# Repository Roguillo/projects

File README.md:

For personal and academic projects

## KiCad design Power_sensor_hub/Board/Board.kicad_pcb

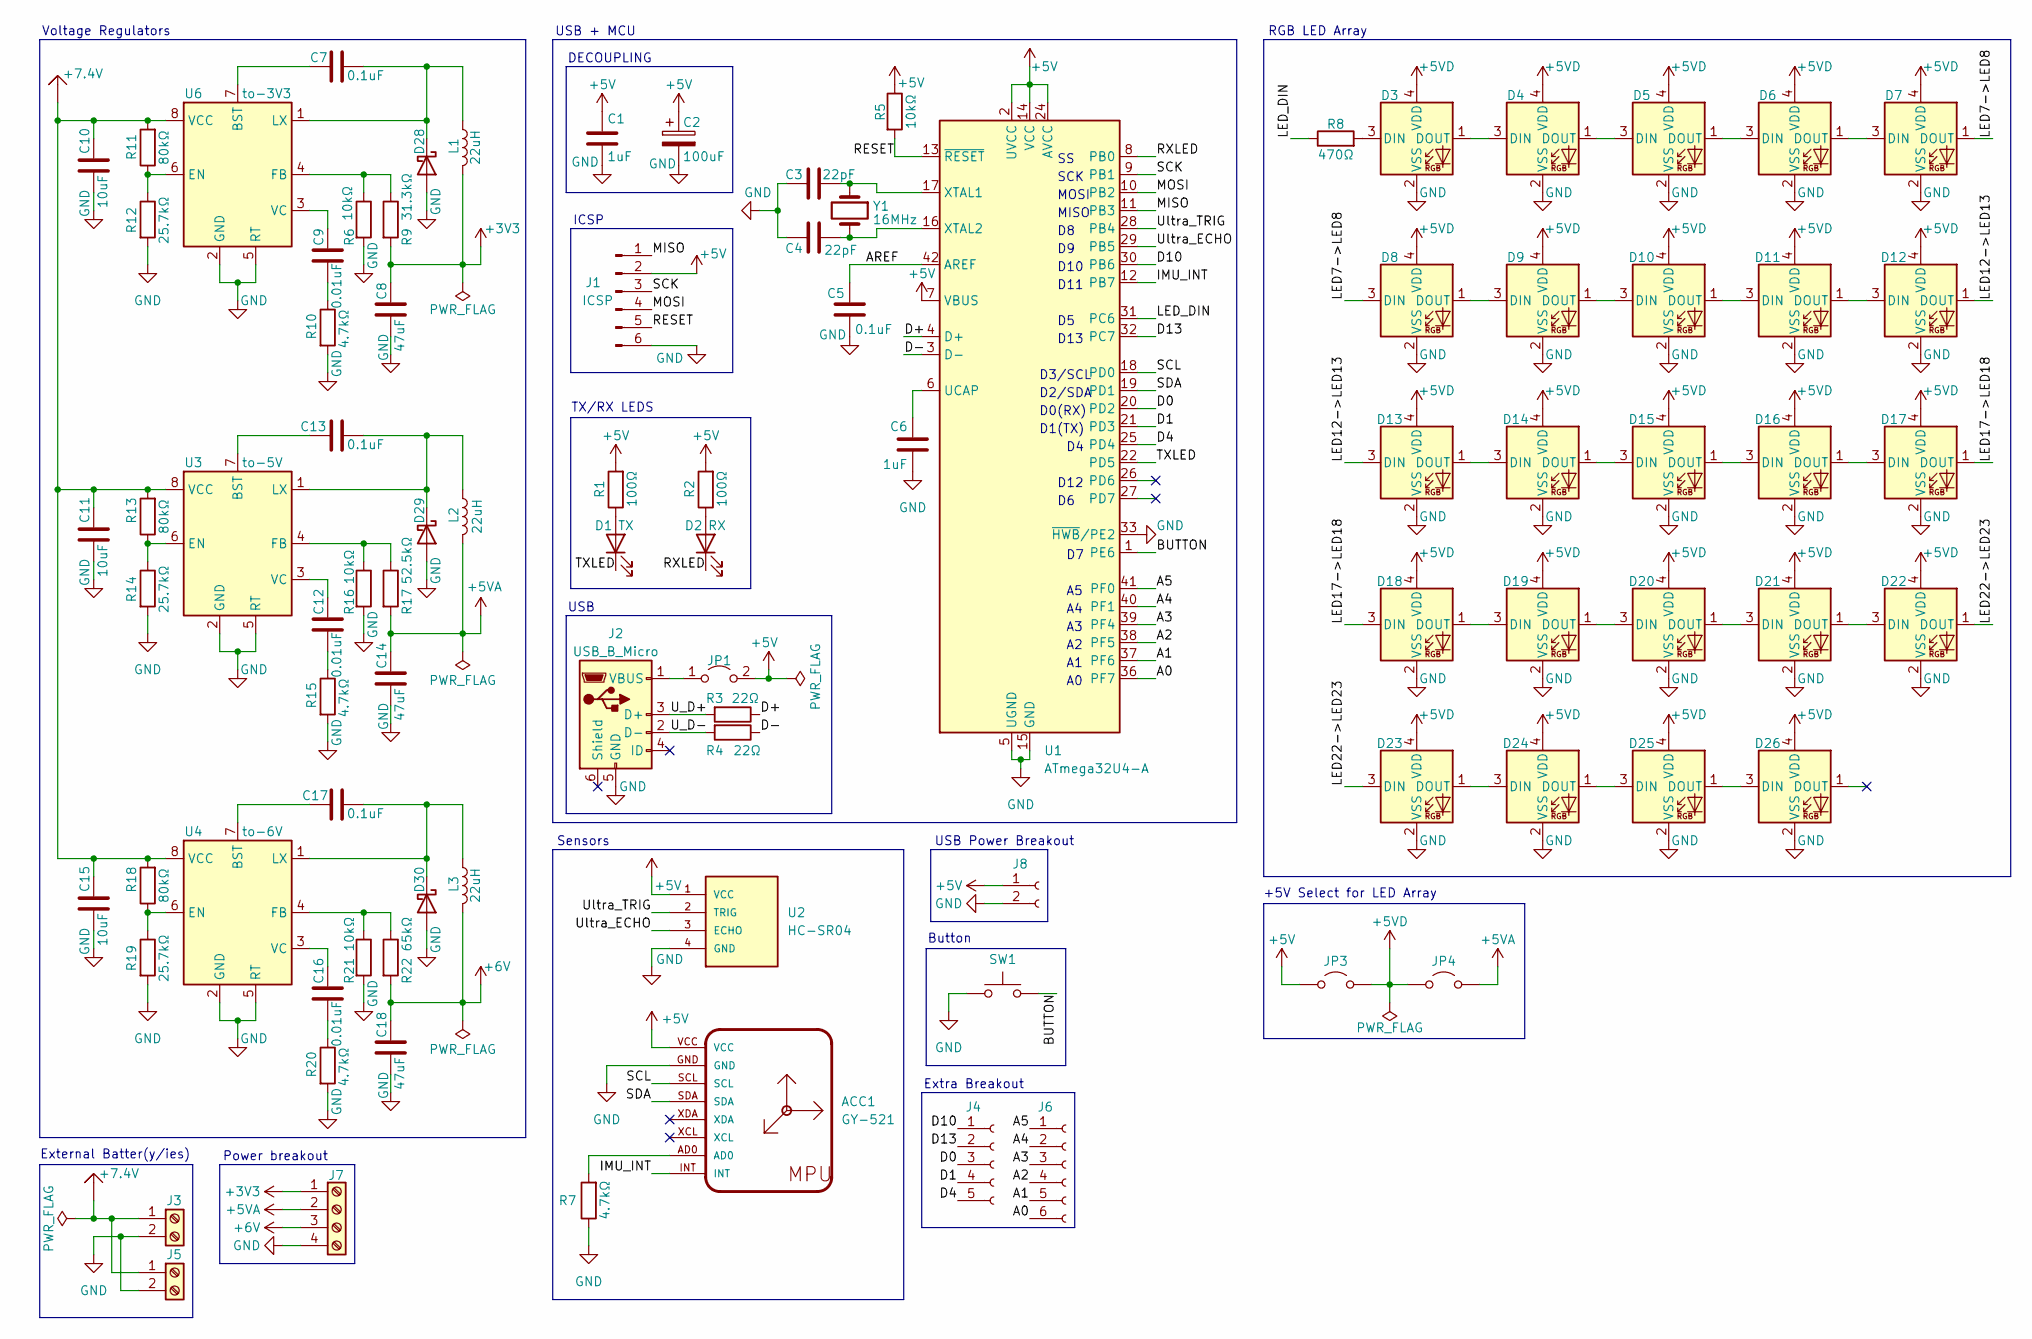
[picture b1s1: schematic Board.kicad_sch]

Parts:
ACC1: GY-521
C1, C6: 1uF; C_0805_2012Metric_Pad1.18x1.45mm_HandSolder
C2: 100uF; CP_Elec_5x5.3
C3, C4: 22pF; C_0805_2012Metric_Pad1.18x1.45mm_HandSolder
C5: 0.1uF; C_0805_2012Metric_Pad1.18x1.45mm_HandSolder
C7, C13, C17: 0.1uF; C_0603_1608Metric_Pad1.08x0.95mm_HandSolder
C8, C14, C18: 47uF; C_1206_3216Metric_Pad1.33x1.80mm_HandSolder
C9, C12, C16: 0.01uF; C_0603_1608Metric_Pad1.08x0.95mm_HandSolder
C10, C11, C15: 10uF; C_1206_3216Metric_Pad1.33x1.80mm_HandSolder
D1: TX; LED_0805_2012Metric_Pad1.15x1.40mm_HandSolder
D2: RX; LED_0805_2012Metric_Pad1.15x1.40mm_HandSolder
D3, D4, D5, D6, D7, D8, D9, D10, D11, D12, D13, D14, D15, D16, D17, D18, D19, D20, D21, D22, D23, D24, D25, D26: SK6812MINI; LED_SK6812MINI_PLCC4_3.5x3.5mm_P1.75mm
D28, D29, D30: D_2114_3652Metric_Pad1.85x3.75mm_HandSolder
J1: ICSP; PinHeader_2x03_P2.54mm_Vertical
J2: USB_B_Micro; USB_Micro-B_GCT_USB3076-30-A
J3, J5: TerminalBlock_Altech_AK300-2_P5.00mm
J4: PinHeader_1x05_P2.54mm_Vertical
J6: PinHeader_1x06_P2.54mm_Vertical
J7: TerminalBlock_Altech_AK300-4_P5.00mm
J8: PinHeader_1x02_P2.54mm_Vertical
JP1: Jumper_2_Open; SolderJumper-2_P1.3mm_Open_TrianglePad1.0x1.5mm
JP3, JP4: SolderJumper-2_P1.3mm_Open_TrianglePad1.0x1.5mm
L1, L2, L3: 22uH; IND_CLF12577NIT_12P8X12P5_TDK-M
R1, R2: 100Ω; R_0805_2012Metric_Pad1.20x1.40mm_HandSolder
R3, R4: 22Ω; R_0805_2012Metric_Pad1.20x1.40mm_HandSolder
R5: 10kΩ; R_0805_2012Metric_Pad1.20x1.40mm_HandSolder
R6, R16, R21: 10kΩ; R_0603_1608Metric_Pad0.98x0.95mm_HandSolder
R7, R10, R15, R20: 4.7kΩ; R_0603_1608Metric_Pad0.98x0.95mm_HandSolder
R8: 470Ω; R_0805_2012Metric_Pad1.20x1.40mm_HandSolder
R9: 31.3kΩ; R_0603_1608Metric_Pad0.98x0.95mm_HandSolder
R11, R13, R18: 80kΩ; R_0402_1005Metric_Pad0.72x0.64mm_HandSolder
R12, R14, R19: 25.7kΩ; R_0603_1608Metric_Pad0.98x0.95mm_HandSolder
R17: 52.5kΩ; R_0603_1608Metric_Pad0.98x0.95mm_HandSolder
R22: 65kΩ; R_0603_1608Metric_Pad0.98x0.95mm_HandSolder
SW1: SW_SPST_PTS647_Sx38
U1: ATmega32U4-A; TQFP-44_10x10mm_P0.8mm
U2: HC-SR04; PinHeader_1x04_P2.54mm_Vertical
U3: to-5V; HTSOP-8-1EP_3.9x4.9mm_P1.27mm_EP2.4x3.2mm_ThermalVias
U4: to-6V; HTSOP-8-1EP_3.9x4.9mm_P1.27mm_EP2.4x3.2mm_ThermalVias
U6: to-3V3; HTSOP-8-1EP_3.9x4.9mm_P1.27mm_EP2.4x3.2mm_ThermalVias
Y1: 16MHz; Crystal_SMD_5032-2Pin_5.0x3.2mm

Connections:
+3V3: C8.1, J7.1, L1.2, R9.2
+5V: ACC1.VCC, C1.1, C2.1, J1.2, J8.1, JP1.2 (B), JP3.1 (A), R1.2, R2.2, R5.1, U1.2 (UVCC), U1.7 (VBUS), U1.14 (VCC), U1.24 (AVCC), U1.34 (VCC), U1.44 (AVCC), U2.1 (VCC)
+5VA: C14.1, J7.2, JP4.2 (B), L2.2, R17.2
+5VD: D3.4 (VDD), D4.4 (VDD), D5.4 (VDD), D6.4 (VDD), D7.4 (VDD), D8.4 (VDD), D9.4 (VDD), D10.4 (VDD), D11.4 (VDD), D12.4 (VDD), D13.4 (VDD), D14.4 (VDD), D15.4 (VDD), D16.4 (VDD), D17.4 (VDD), D18.4 (VDD), D19.4 (VDD), D20.4 (VDD), D21.4 (VDD), D22.4 (VDD), D23.4 (VDD), D24.4 (VDD), D25.4 (VDD), D26.4 (VDD), JP3.2 (B), JP4.1 (A)
+6V: C18.1, J7.3, L3.2, R22.2
+7.4V: C10.1, C11.1, C15.1, J3.1, J5.1, R11.2, R13.2, R18.2, U3.8 (VCC), U4.8 (VCC), U6.8 (VCC)
/A0: J6.6, U1.36 (PF7)
/A1: J6.5, U1.37 (PF6)
/A2: J6.4, U1.38 (PF5)
/A3: J6.3, U1.39 (PF4)
/A4: J6.2, U1.40 (PF1)
/A5: J6.1, U1.41 (PF0)
/AREF: C5.1, U1.42 (AREF)
/BUTTON: SW1.2, U1.1 (PE6)
/D0: J4.3, U1.20 (PD2)
/D1: J4.4, U1.21 (PD3)
/D4: J4.5, U1.25 (PD4)
/D10: J4.1, U1.30 (PB6)
/D13: J4.2, U1.32 (PC7)
/D+: R3.1, U1.4 (D+)
/D-: R4.1, U1.3 (D-)
/IMU_INT: ACC1.INT, U1.12 (PB7)
/LED7->LED8: D7.1 (DOUT), D8.3 (DIN)
/LED12->LED13: D12.1 (DOUT), D13.3 (DIN)
/LED17->LED18: D17.1 (DOUT), D18.3 (DIN)
/LED22->LED23: D22.1 (DOUT), D23.3 (DIN)
/LED_DIN: R8.1, U1.31 (PC6)
/MISO: J1.1, U1.11 (PB3)
/MOSI: J1.4, U1.10 (PB2)
/RESET: J1.5, R5.2, U1.13 (~RESET)
/RXLED: D2.1 (K), U1.8 (PB0)
/SCK: J1.3, U1.9 (PB1)
/SCL: ACC1.SCL, U1.18 (PD0)
/SDA: ACC1.SDA, U1.19 (PD1)
/TXLED: D1.1 (K), U1.22 (PD5)
/U_D+: J2.3 (D+), R3.2
/U_D-: J2.2 (D-), R4.2
/Ultra_ECHO: U1.29 (PB5), U2.3 (ECHO)
/Ultra_TRIG: U1.28 (PB4), U2.2 (TRIG)
BST_3V3: C7.1, U6.7 (BST)
BST_5V: C13.1, U3.7 (BST)
BST_6V: C17.1, U4.7 (BST)
GND: ACC1.GND, C1.2, C2.2, C3.2, C4.2, C5.2, C6.2, C8.2, C10.2, C11.2, C14.2, C15.2, C18.2, D3.2 (VSS), D4.2 (VSS), D5.2 (VSS), D6.2 (VSS), D7.2 (VSS), D8.2 (VSS), D9.2 (VSS), D10.2 (VSS), D11.2 (VSS), D12.2 (VSS), D13.2 (VSS), D14.2 (VSS), D15.2 (VSS), D16.2 (VSS), D17.2 (VSS), D18.2 (VSS), D19.2 (VSS), D20.2 (VSS), D21.2 (VSS), D22.2 (VSS), D23.2 (VSS), D24.2 (VSS), D25.2 (VSS), D26.2 (VSS), D28.2 (A), D29.2 (A), D30.2 (A), J1.6, J2.5 (GND), J3.2, J5.2, J7.4, J8.2, R6.2, R7.1, R10.2, R12.2, R14.2, R15.2, R16.2, R19.2, R20.2, R21.2, SW1.1, U1.5 (UGND), U1.15 (GND), U1.23 (GND), U1.33 (~HWB/PE2), U1.35 (GND), U1.43 (GND), U2.4 (GND), U3.2 (GND), U3.5 (RT), U3.9, U4.2 (GND), U4.5 (RT), U4.9, U6.2 (GND), U6.5 (RT), U6.9; also elsewhere on the board
unnamed: ACC1.AD0, R7.2
unnamed: C9.2, R10.1
unnamed: C12.2, R15.1
unnamed: C16.2, R20.1
unnamed: D1.2 (A), R1.1
unnamed: D2.2 (A), R2.1
unnamed: D3.3 (DIN), R8.2
unnamed: D3.1 (DOUT), D4.3 (DIN)
unnamed: D4.1 (DOUT), D5.3 (DIN)
unnamed: D5.1 (DOUT), D6.3 (DIN)
unnamed: D6.1 (DOUT), D7.3 (DIN)
unnamed: D8.1 (DOUT), D9.3 (DIN)
unnamed: D9.1 (DOUT), D10.3 (DIN)
unnamed: D10.1 (DOUT), D11.3 (DIN)
unnamed: D11.1 (DOUT), D12.3 (DIN)
unnamed: D13.1 (DOUT), D14.3 (DIN)
unnamed: D14.1 (DOUT), D15.3 (DIN)
unnamed: D15.1 (DOUT), D16.3 (DIN)
unnamed: D16.1 (DOUT), D17.3 (DIN)
unnamed: D18.1 (DOUT), D19.3 (DIN)
unnamed: D19.1 (DOUT), D20.3 (DIN)
unnamed: D20.1 (DOUT), D21.3 (DIN)
unnamed: D21.1 (DOUT), D22.3 (DIN)
unnamed: D23.1 (DOUT), D24.3 (DIN)
unnamed: D24.1 (DOUT), D25.3 (DIN)
unnamed: D25.1 (DOUT), D26.3 (DIN)
unnamed: C7.2, D28.1 (K), L1.1, U6.1 (LX)
unnamed: C13.2, D29.1 (K), L2.1, U3.1 (LX)
unnamed: C17.2, D30.1 (K), L3.1, U4.1 (LX)
unnamed: J2.1 (VBUS), JP1.1 (A)
unnamed: C6.1, U1.6 (UCAP)
unnamed: C3.1, U1.17 (XTAL1), Y1.1
unnamed: C4.1, U1.16 (XTAL2), Y1.2
unnamed: R13.1, R14.1, U3.6 (EN)
unnamed: R16.1, R17.1, U3.4 (FB)
unnamed: C12.1, U3.3 (VC)
unnamed: R18.1, R19.1, U4.6 (EN)
unnamed: R21.1, R22.1, U4.4 (FB)
unnamed: C16.1, U4.3 (VC)
unnamed: R11.1, R12.1, U6.6 (EN)
unnamed: R6.1, R9.1, U6.4 (FB)
unnamed: C9.1, U6.3 (VC)

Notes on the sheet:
D13
RGB LED Array
D11
USB
Voltage Regulators
D0(RX)
D2/SDA
External Batter(y/ies)
SCK
DECOUPLING
Power breakout
MOSI
USB + MCU
Extra Breakout
Button
USB Power Breakout
D3/SCL
Sensors
MISO
D10
TX/RX LEDS
ICSP
D12
D1(TX)
+5V Select for LED Array

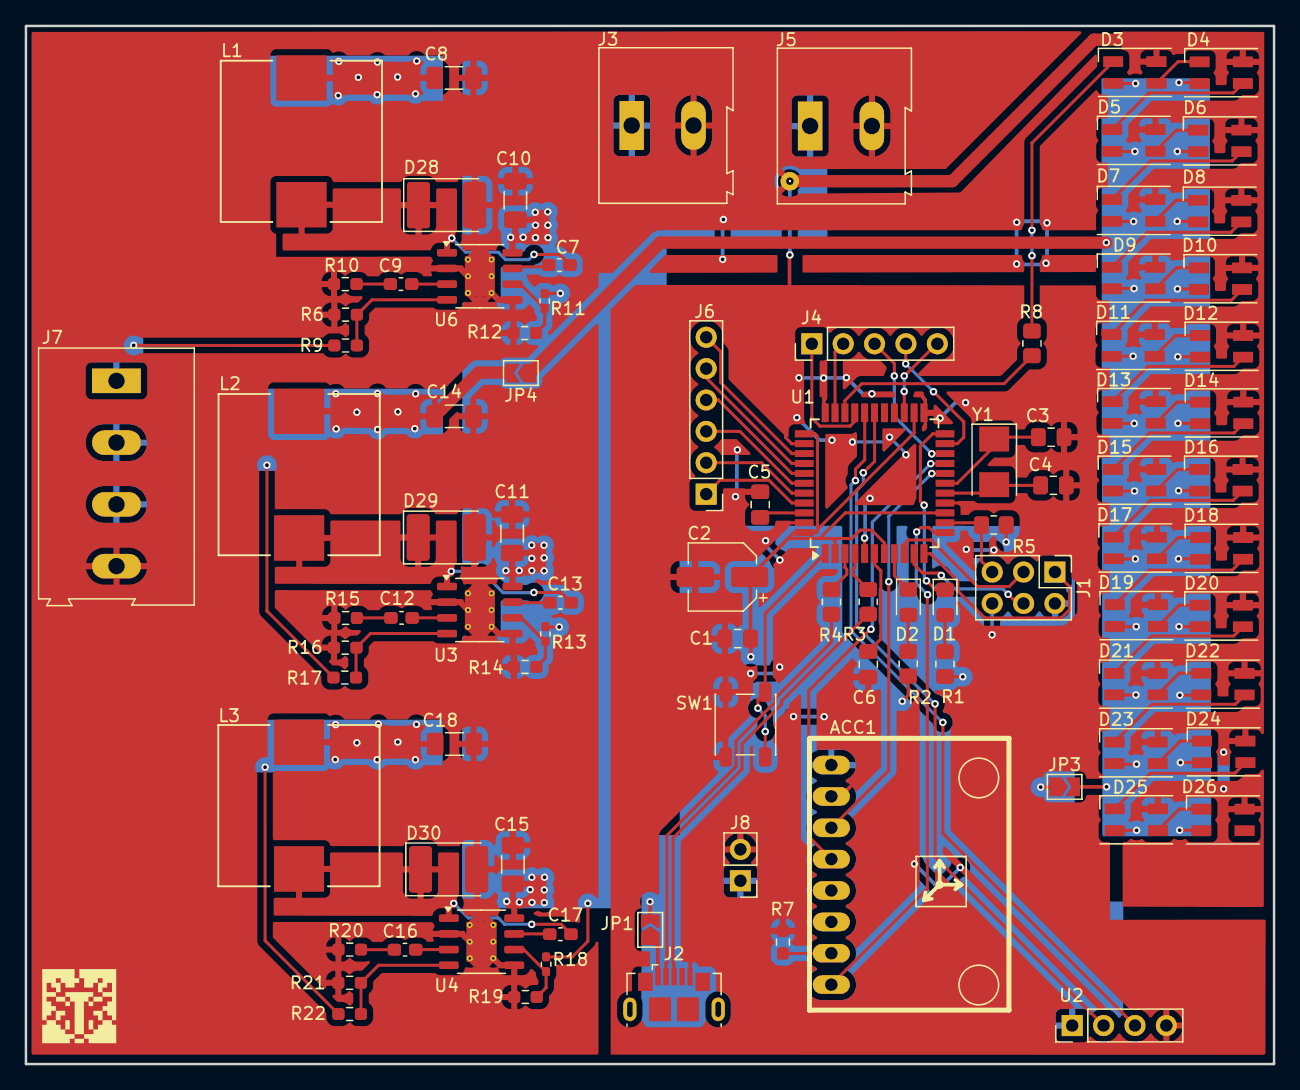
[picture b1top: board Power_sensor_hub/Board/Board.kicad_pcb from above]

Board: 2 copper layers, 101.0 x 84.0 mm, 92 parts (0 on the bottom side), 85 nets.

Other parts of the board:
.: STAR

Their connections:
GND: ..3; also elsewhere on the board

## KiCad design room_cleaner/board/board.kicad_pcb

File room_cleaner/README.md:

A general-purpose differential drive base robot. Planning on implementing CV and possibly an arm in the future.

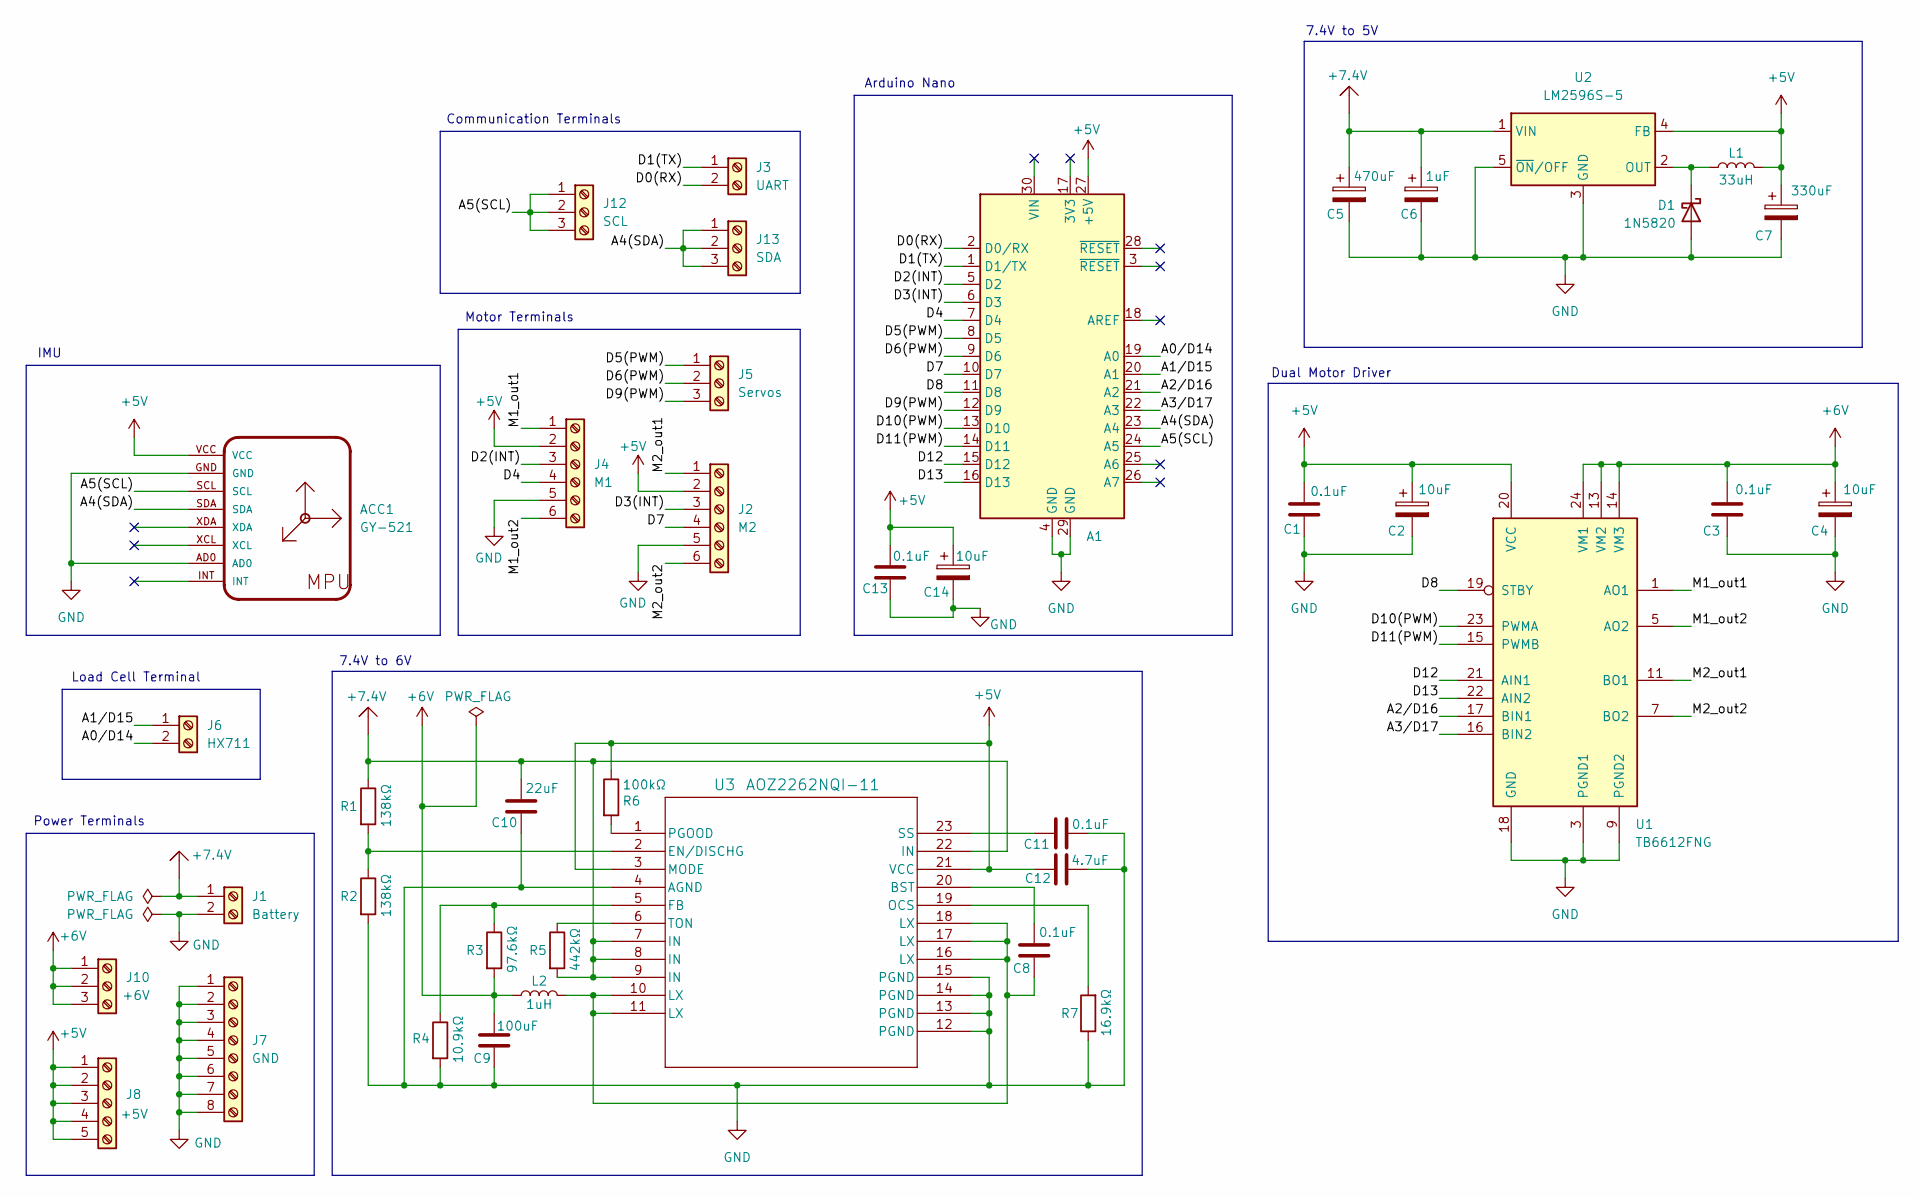
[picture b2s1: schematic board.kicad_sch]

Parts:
A1: Arduino_Nano
ACC1: GY-521
C1, C3, C8, C11, C13: 0.1uF; C_0402_1005Metric_Pad0.74x0.62mm_HandSolder
C2, C4, C14: 10uF; C_1206_3216Metric_Pad1.33x1.80mm_HandSolder
C5: 470uF; CP_Radial_D6.3mm_P2.50mm
C6: 1uF; C_0603_1608Metric_Pad1.08x0.95mm_HandSolder
C7: 330uF; CP_Radial_D6.3mm_P2.50mm
C9: 100uF; C_1206_3216Metric_Pad1.33x1.80mm_HandSolder
C10: 22uF; C_0603_1608Metric_Pad1.08x0.95mm_HandSolder
C12: 4.7uF; C_0603_1608Metric_Pad1.08x0.95mm_HandSolder
D1: 1N5820; D_DO-201AD_P15.24mm_Horizontal
J1: Battery; TerminalBlock_Altech_AK300-2_P5.00mm
J2: M2; TerminalBlock_bornier-6_P5.08mm
J3: UART; TerminalBlock_Altech_AK300-2_P5.00mm
J4: M1; TerminalBlock_bornier-6_P5.08mm
J5: Servos; TerminalBlock_Altech_AK300-3_P5.00mm
J6: HX711; TerminalBlock_Altech_AK300-2_P5.00mm
J7: GND; TerminalBlock_bornier-8_P5.08mm
J8: +5V; TerminalBlock_bornier-5_P5.08mm
J10: +6V; TerminalBlock_Altech_AK300-3_P5.00mm
J12: SCL; TerminalBlock_Altech_AK300-3_P5.00mm
J13: SDA; TerminalBlock_Altech_AK300-3_P5.00mm
L1: 33uH; L_6.3x6.3_H3
L2: 1uH; L_0805_2012Metric_Pad1.15x1.40mm_HandSolder
R1, R2: 138kΩ; R_0603_1608Metric_Pad0.98x0.95mm_HandSolder
R3: 97.6kΩ; R_0402_1005Metric_Pad0.72x0.64mm_HandSolder
R4: 10.9kΩ; R_0805_2012Metric_Pad1.20x1.40mm_HandSolder
R5: 442kΩ; R_0402_1005Metric_Pad0.72x0.64mm_HandSolder
R6: 100kΩ; R_0402_1005Metric_Pad0.72x0.64mm_HandSolder
R7: 16.9kΩ; R_0402_1005Metric_Pad0.72x0.64mm_HandSolder
U1: TB6612FNG; SSOP-24_5.3x8.2mm_P0.65mm
U2: LM2596S-5; TO-263-5_TabPin3
U3: AOZ2262NQI-11; AOZ226NQI-11

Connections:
+5V: A1.27 (+5V), ACC1.VCC, C1.1, C2.1, C7.1, C12.1, C13.1, C14.1, J2.2, J4.2, J8.1, J8.2, J8.3, J8.4, J8.5, L1.2, R6.1, U1.20 (VCC), U2.4 (FB), U3.3 (MODE), U3.21 (VCC)
+6V: C3.1, C4.1, C9.1, J10.1, J10.2, J10.3, L2.1, R3.2, U1.13 (VM2), U1.14 (VM3), U1.24 (VM1)
+7.4V: C5.1, C6.1, C10.1, J1.1, R1.1, R5.2, U2.1 (VIN), U3.7 (IN), U3.8 (IN), U3.9 (IN), U3.22 (IN), U3.24
/A0/D14: A1.19 (A0), J6.2
/A1/D15: A1.20 (A1), J6.1
/A2/D16: A1.21 (A2), U1.17 (BIN1)
/A3/D17: A1.22 (A3), U1.16 (BIN2)
/A4(SDA): A1.23 (A4), ACC1.SDA, J13.1, J13.2, J13.3
/A5(SCL): A1.24 (A5), ACC1.SCL, J12.1, J12.2, J12.3
/D0(RX): A1.2 (D0/RX), J3.2
/D1(TX): A1.1 (D1/TX), J3.1
/D2(INT): A1.5 (D2), J4.3
/D3(INT): A1.6 (D3), J2.3
/D4: A1.7 (D4), J4.4
/D5(PWM): A1.8 (D5), J5.1
/D6(PWM): A1.9 (D6), J5.2
/D7: A1.10 (D7), J2.4
/D8: A1.11 (D8), U1.19 (STBY)
/D9(PWM): A1.12 (D9), J5.3
/D10(PWM): A1.13 (D10), U1.23 (PWMA)
/D11(PWM): A1.14 (D11), U1.15 (PWMB)
/D12: A1.15 (D12), U1.21 (AIN1)
/D13: A1.16 (D13), U1.22 (AIN2)
/M1_out1: J4.1, U1.1 (AO1), U1.2 (AO1)
/M1_out2: J4.6, U1.5 (AO2), U1.6 (AO2)
/M2_out1: J2.1, U1.11 (BO1), U1.12 (BO1)
/M2_out2: J2.6, U1.7 (BO2), U1.8 (BO2)
GND: A1.4 (GND), A1.29 (GND), ACC1.AD0, ACC1.GND, C1.2, C2.2, C3.2, C4.2, C5.2, C6.2, C7.2, C9.2, C10.2, C11.2, C12.2, C13.2, C14.2, D1.2 (A), J1.2, J2.5, J4.5, J7.1, J7.2, J7.3, J7.4, J7.5, J7.6, J7.7, J7.8, R2.2, R4.2, R7.1, U1.3 (PGND1), U1.4 (PGND1), U1.9 (PGND2), U1.10 (PGND2), U1.18 (GND), U2.3 (GND), U2.5 (~ON/OFF), U3.4 (AGND), U3.12 (PGND), U3.13 (PGND), U3.14 (PGND), U3.15 (PGND)
unnamed: C8.1, L2.2, U3.10 (LX), U3.11 (LX), U3.16 (LX), U3.17 (LX), U3.18 (LX), U3.25
unnamed: D1.1 (K), L1.1, U2.2 (OUT)
unnamed: C8.2, U3.20 (BST)
unnamed: R1.2, R2.1, U3.2 (EN/DISCHG)
unnamed: R3.1, R4.1, U3.5 (FB)
unnamed: R7.2, U3.19 (OCS)
unnamed: R6.2, U3.1 (PGOOD)
unnamed: C11.1, U3.23 (SS)
unnamed: R5.1, U3.6 (TON)

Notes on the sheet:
7.4V to 6V
Communication Terminals
Dual Motor Driver
7.4V to 5V
Arduino Nano
Power Terminals
Motor Terminals
Load Cell Terminal
IMU

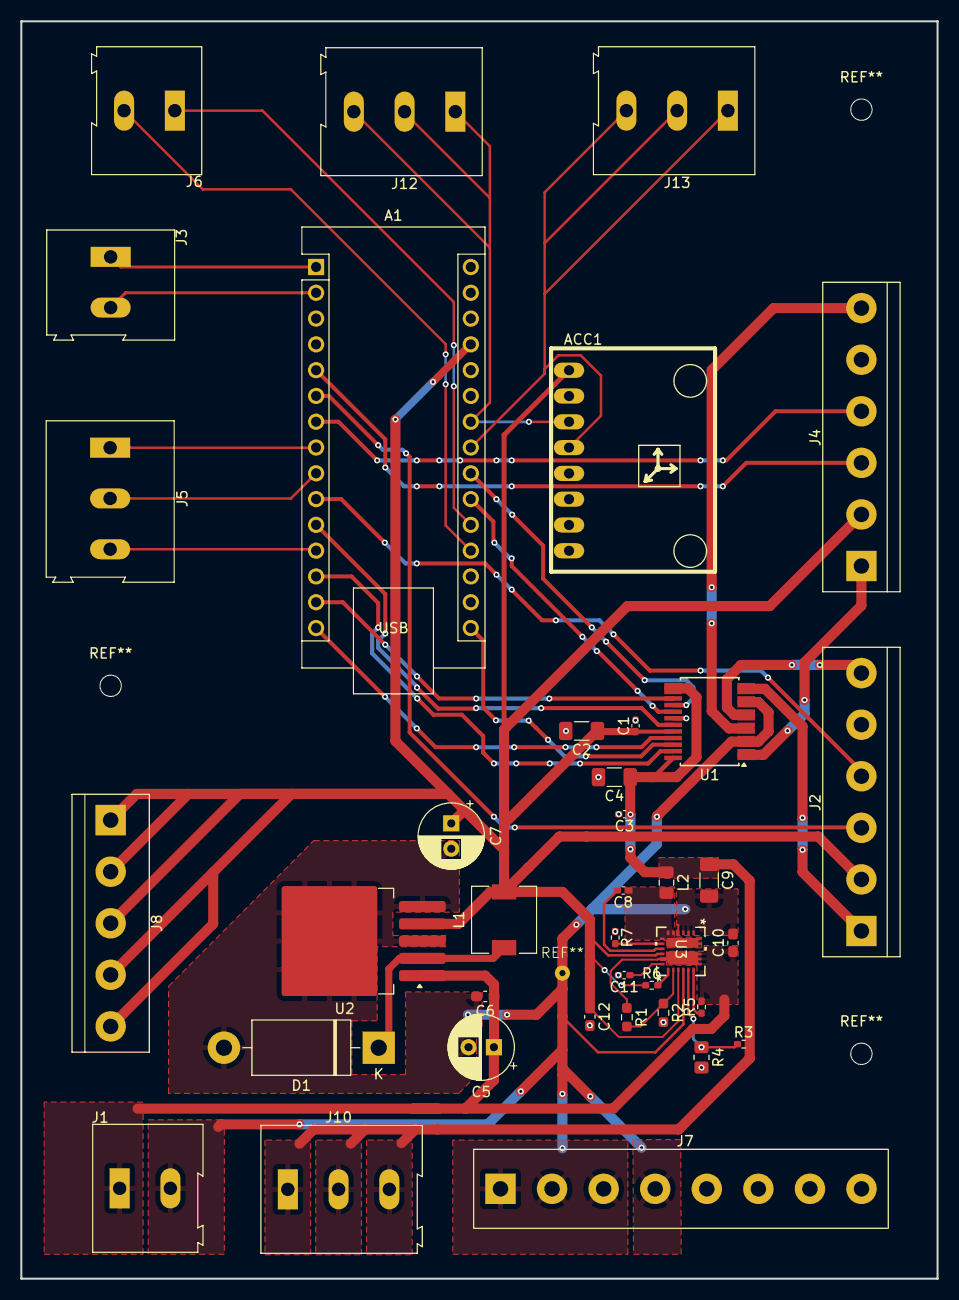
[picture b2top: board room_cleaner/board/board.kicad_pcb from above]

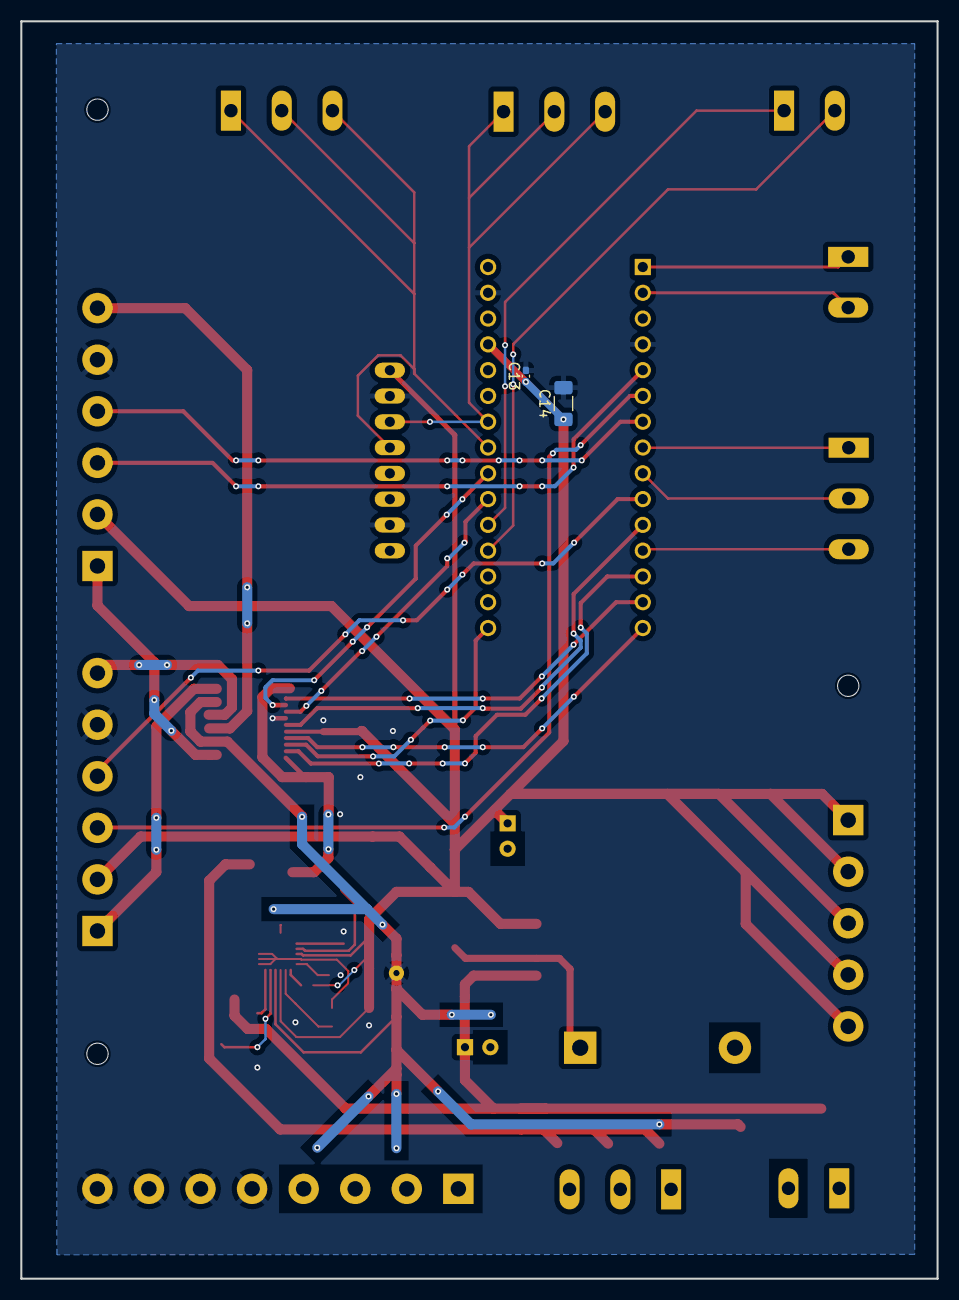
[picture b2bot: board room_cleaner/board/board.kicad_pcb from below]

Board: 2 copper layers, 90.2 x 123.9 mm, 40 parts (2 on the bottom side), 37 nets.

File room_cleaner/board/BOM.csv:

Id,Designator,Footprint,Quantity,Designation,Supplier and ref,
1,J1,TerminalBlock_Altech_AK300-2_P5.00mm,1,Battery,~,
2,C6,C_0603_1608Metric_Pad1.08x0.95mm_HandSolder,1,1uF,~,
3,J7,TerminalBlock_bornier-8_P5.08mm,1,GND,~,
4,J10,TerminalBlock_Altech_AK300-3_P5.00mm,1,+6V,~,
5,J5,TerminalBlock_Altech_AK300-3_P5.00mm,1,Servos,~,
6,U2,TO-263-5_TabPin3,1,LM2596S-5,~,
7,REF**,STAR,1,STAR,~,
8,R3,R_0402_1005Metric_Pad0.72x0.64mm_HandSolder,1,97.6k?,~,
9,U1,SSOP-24_5.3x8.2mm_P0.65mm,1,TB6612FNG,~,
10,A1,Arduino_Nano,1,~,~,
11,J4,TerminalBlock_bornier-6_P5.08mm,1,M1,~,
12,J2,TerminalBlock_bornier-6_P5.08mm,1,M2,~,
13,R5,R_0402_1005Metric_Pad0.72x0.64mm_HandSolder,1,442k?,~,
14,J8,TerminalBlock_bornier-5_P5.08mm,1,+5V,~,
15,"C8,C1,C11,C3,C13",C_0402_1005Metric_Pad0.74x0.62mm_HandSolder,5,0.1uF,~,
16,C10,C_0603_1608Metric_Pad1.08x0.95mm_HandSolder,1,22uF,~,
17,C9,C_1206_3216Metric_Pad1.33x1.80mm_HandSolder,1,100uF,~,
18,"C2,C4,C14",C_1206_3216Metric_Pad1.33x1.80mm_HandSolder,3,10uF,~,
19,J3,TerminalBlock_Altech_AK300-2_P5.00mm,1,UART,~,
20,L1,L_6.3x6.3_H3,1,33uH,~,
21,R7,R_0402_1005Metric_Pad0.72x0.64mm_HandSolder,1,16.9k?,~,
22,C12,C_0603_1608Metric_Pad1.08x0.95mm_HandSolder,1,4.7uF,~,
23,J12,TerminalBlock_Altech_AK300-3_P5.00mm,1,SCL,~,
24,ACC1,GY-521,1,GY-521,~,
25,"R1,R2",R_0603_1608Metric_Pad0.98x0.95mm_HandSolder,2,138k?,~,
26,L2,L_0805_2012Metric_Pad1.15x1.40mm_HandSolder,1,1uH,~,
27,R4,R_0805_2012Metric_Pad1.20x1.40mm_HandSolder,1,10.9k?,~,
28,J6,TerminalBlock_Altech_AK300-2_P5.00mm,1,HX711,~,
29,U3,AOZ226NQI-11,1,AOZ2262NQI-11,~,
30,C5,CP_Radial_D6.3mm_P2.50mm,1,470uF,~,
31,D1,D_DO-201AD_P15.24mm_Horizontal,1,1N5820,~,
32,R6,R_0402_1005Metric_Pad0.72x0.64mm_HandSolder,1,100k?,~,
33,J13,TerminalBlock_Altech_AK300-3_P5.00mm,1,SDA,~,
34,C7,CP_Radial_D6.3mm_P2.50mm,1,330uF,~,

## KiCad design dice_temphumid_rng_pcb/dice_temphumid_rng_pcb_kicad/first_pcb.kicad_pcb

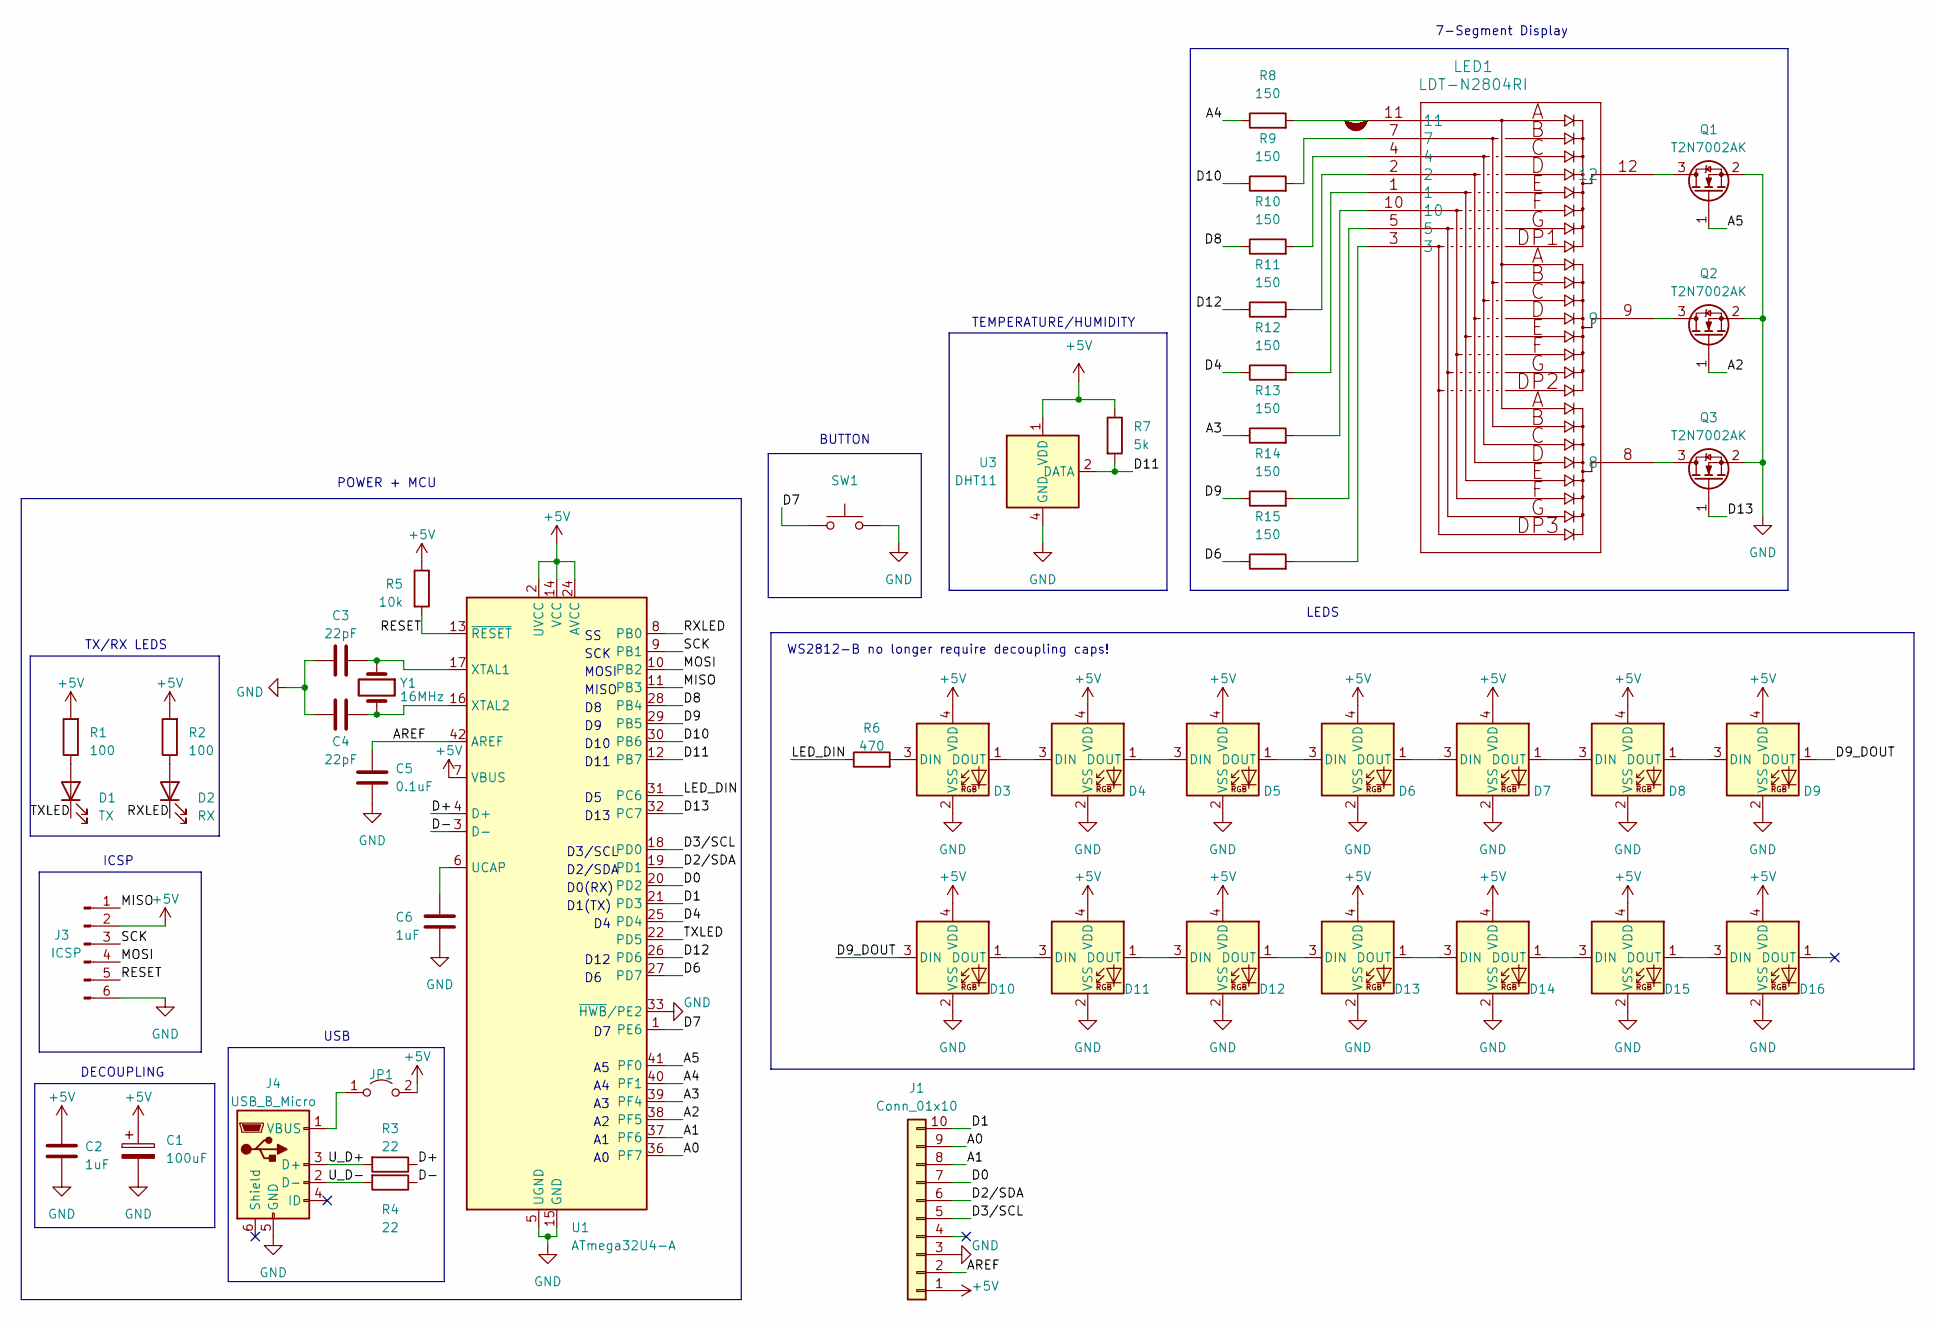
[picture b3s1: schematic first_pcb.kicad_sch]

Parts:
C1: 100uF; CP_Elec_5x5.3
C2, C6: 1uF; C_0805_2012Metric_Pad1.18x1.45mm_HandSolder
C3, C4: 22pF; C_0805_2012Metric_Pad1.18x1.45mm_HandSolder
C5: 0.1uF; C_0805_2012Metric_Pad1.18x1.45mm_HandSolder
D1: TX; LED_0805_2012Metric_Pad1.15x1.40mm_HandSolder
D2: RX; LED_0805_2012Metric_Pad1.15x1.40mm_HandSolder
D3, D4, D5, D6, D7, D8, D9, D10, D11, D12, D13, D14, D15, D16: SK6812MINI; LED_SK6812MINI_PLCC4_3.5x3.5mm_P1.75mm
J1: Conn_01x10; PinHeader_1x10_P2.54mm_Vertical
J3: ICSP; PinHeader_2x03_P2.54mm_Vertical
J4: USB_B_Micro; USB_Micro-B_GCT_USB3076-30-A
JP1: Jumper_2_Open; SolderJumper-2_P1.3mm_Open_TrianglePad1.0x1.5mm
LED1: LDT-N2804RI
Q1, Q2, Q3: T2N7002AK; SOT-23
R1, R2: 100; R_0805_2012Metric_Pad1.20x1.40mm_HandSolder
R3, R4: 22; R_0805_2012Metric_Pad1.20x1.40mm_HandSolder
R5: 10k; R_0805_2012Metric_Pad1.20x1.40mm_HandSolder
R6: 470; R_0805_2012Metric_Pad1.20x1.40mm_HandSolder
R7: 5k; R_0805_2012Metric_Pad1.20x1.40mm_HandSolder
R8, R9, R10, R11, R12, R13, R14, R15: 150; R_0805_2012Metric_Pad1.20x1.40mm_HandSolder
SW1: SW_SPST_PTS647_Sx38
U1: ATmega32U4-A; TQFP-44_10x10mm_P0.8mm
U3: DHT11; Aosong_DHT11_5.5x12.0_P2.54mm
Y1: 16MHz; Crystal_SMD_5032-2Pin_5.0x3.2mm

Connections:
+5V: C1.1, C2.1, D3.4 (VDD), D4.4 (VDD), D5.4 (VDD), D6.4 (VDD), D7.4 (VDD), D8.4 (VDD), D9.4 (VDD), D10.4 (VDD), D11.4 (VDD), D12.4 (VDD), D13.4 (VDD), D14.4 (VDD), D15.4 (VDD), D16.4 (VDD), J1.1, J3.2, JP1.2 (B), R1.2, R2.2, R5.1, R7.1, U1.2 (UVCC), U1.7 (VBUS), U1.14 (VCC), U1.24 (AVCC), U1.34 (VCC), U1.44 (AVCC), U3.1 (VDD)
/A0: J1.9, U1.36 (PF7)
/A1: J1.8, U1.37 (PF6)
/A2: Q2.1 (G), U1.38 (PF5)
/A3: R13.1, U1.39 (PF4)
/A4: R8.1, U1.40 (PF1)
/A5: Q1.1 (G), U1.41 (PF0)
/AREF: C5.1, J1.2, U1.42 (AREF)
/D0: J1.7, U1.20 (PD2)
/D1: J1.10, U1.21 (PD3)
/D2/SDA: J1.6, U1.19 (PD1)
/D3/SCL: J1.5, U1.18 (PD0)
/D4: R12.1, U1.25 (PD4)
/D6: R15.1, U1.27 (PD7)
/D7: SW1.1, U1.1 (PE6)
/D8: R10.1, U1.28 (PB4)
/D9: R14.1, U1.29 (PB5)
/D9_DOUT: D9.1 (DOUT), D10.3 (DIN)
/D10: R9.1, U1.30 (PB6)
/D11: R7.2, U1.12 (PB7), U3.2 (DATA)
/D12: R11.1, U1.26 (PD6)
/D13: Q3.1 (G), U1.32 (PC7)
/D+: R3.1, U1.4 (D+)
/D-: R4.1, U1.3 (D-)
/LED_DIN: R6.1, U1.31 (PC6)
/MISO: J3.1, U1.11 (PB3)
/MOSI: J3.4, U1.10 (PB2)
/RESET: J3.5, R5.2, U1.13 (~RESET)
/RXLED: D2.1 (K), U1.8 (PB0)
/SCK: J3.3, U1.9 (PB1)
/TXLED: D1.1 (K), U1.22 (PD5)
/U_D+: J4.3 (D+), R3.2
/U_D-: J4.2 (D-), R4.2
GND: C1.2, C2.2, C3.2, C4.2, C5.2, C6.2, D3.2 (VSS), D4.2 (VSS), D5.2 (VSS), D6.2 (VSS), D7.2 (VSS), D8.2 (VSS), D9.2 (VSS), D10.2 (VSS), D11.2 (VSS), D12.2 (VSS), D13.2 (VSS), D14.2 (VSS), D15.2 (VSS), D16.2 (VSS), J1.3, J3.6, J4.5 (GND), Q1.2 (S), Q2.2 (S), Q3.2 (S), SW1.2, U1.5 (UGND), U1.15 (GND), U1.23 (GND), U1.33 (~HWB/PE2), U1.35 (GND), U1.43 (GND), U3.4 (GND)
unnamed: D1.2 (A), R1.1
unnamed: D2.2 (A), R2.1
unnamed: D3.3 (DIN), R6.2
unnamed: D3.1 (DOUT), D4.3 (DIN)
unnamed: D4.1 (DOUT), D5.3 (DIN)
unnamed: D5.1 (DOUT), D6.3 (DIN)
unnamed: D6.1 (DOUT), D7.3 (DIN)
unnamed: D7.1 (DOUT), D8.3 (DIN)
unnamed: D8.1 (DOUT), D9.3 (DIN)
unnamed: D10.1 (DOUT), D11.3 (DIN)
unnamed: D11.1 (DOUT), D12.3 (DIN)
unnamed: D12.1 (DOUT), D13.3 (DIN)
unnamed: D13.1 (DOUT), D14.3 (DIN)
unnamed: D14.1 (DOUT), D15.3 (DIN)
unnamed: D15.1 (DOUT), D16.3 (DIN)
unnamed: J4.1 (VBUS), JP1.1 (A)
unnamed: LED1.1, R12.2
unnamed: LED1.2, R11.2
unnamed: LED1.3, R15.2
unnamed: LED1.4, R10.2
unnamed: LED1.5, R14.2
unnamed: LED1.7, R9.2
unnamed: LED1.10, R13.2
unnamed: LED1.11, R8.2
unnamed: LED1.12, Q1.3 (D)
unnamed: LED1.9, Q2.3 (D)
unnamed: LED1.8, Q3.3 (D)
unnamed: C6.1, U1.6 (UCAP)
unnamed: C3.1, U1.17 (XTAL1), Y1.1
unnamed: C4.1, U1.16 (XTAL2), Y1.2

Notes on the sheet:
MOSI
D2/SDA
LEDS
BUTTON
D11
D3/SCL
USB
DECOUPLING
D1(TX)
D13
WS2812-B no longer require decoupling caps!
MISO
D10
POWER + MCU
TEMPERATURE/HUMIDITY
TX/RX LEDS
ICSP
7-Segment Display
SCK
D12
D0(RX)

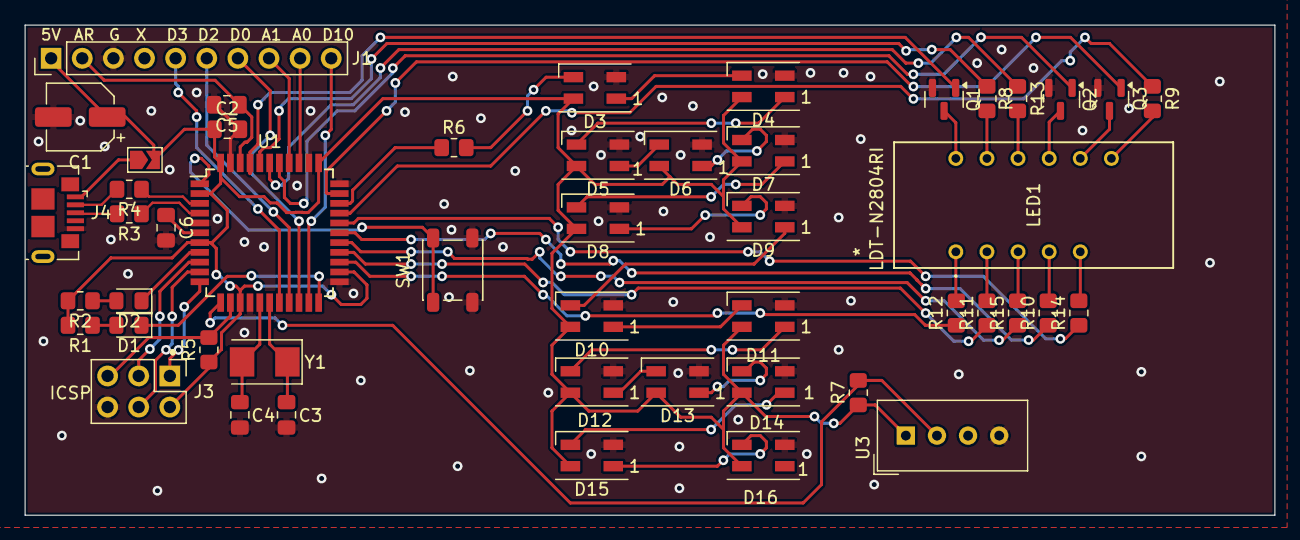
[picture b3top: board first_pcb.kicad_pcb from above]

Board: 2 copper layers, 102.0 x 40.0 mm, 49 parts (0 on the bottom side), 64 nets.

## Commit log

2024-12-28 start
2024-12-28 code for first pcb
2024-12-28 added kicad files and put into the same subdirectory with the code
2024-12-28 removed leftover code file
2025-01-01 added celsius/fahrenheit toggle with longer press
2025-01-18 made dice() random rather than just pseudo-random, added short startup animation
2025-01-18 fixed dice(), added short startup animation
2025-01-18 removed duplicate code file
2025-01-21 Incorporated LED array into startup animation
2025-01-25 added .gitignore and LICENSE files, and a very brief description in README.md
2025-01-25 added pictures
2025-08-08 added KiCAD files
2025-08-08 added board-relevant datasheets, project README, and project .gitignore
2025-08-08 forgot to add motor driver datasheet
2025-08-08 grouping files
2025-08-08 removed duplicate files
2025-08-29 adding code for robotics course projects
2025-08-29 small change to README.md
2025-08-29 removed connection to old course repo
2025-08-29 changed to final/most recent branch of course project
2025-09-06 Added README.md files for RBE projects
2025-09-06 moved README.md file
2025-10-27 pushed RBE 3001 project
2025-10-28 pushed power hub and sensor pcb design, pending board shipment, assembly and code
2025-10-30 minor changes
2025-11-27 created skeleton/starter code
2025-11-28 not much actual progress; learning about how OO C++ is combined with FreeRTOS
2025-11-30 better structure; did away with separate .cpp files for modules

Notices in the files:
parts and their libraries:
Copyright 2016 Accelerated Designs. All rights reserved.
